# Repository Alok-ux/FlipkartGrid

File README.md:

# Flipkart Grid (Robotics)

TODO: Fill the readme
- [ ] Description of the project/event and upload the problem statement
- [ ] Team Description and also mention mentors
- [ ] Prerequisites and Installation procedure
- [ ] Run Instructions

Credits:
- [Multi-Agent Path Planning in Python
](https://github.com/atb033/multi_agent_path_planning.git)

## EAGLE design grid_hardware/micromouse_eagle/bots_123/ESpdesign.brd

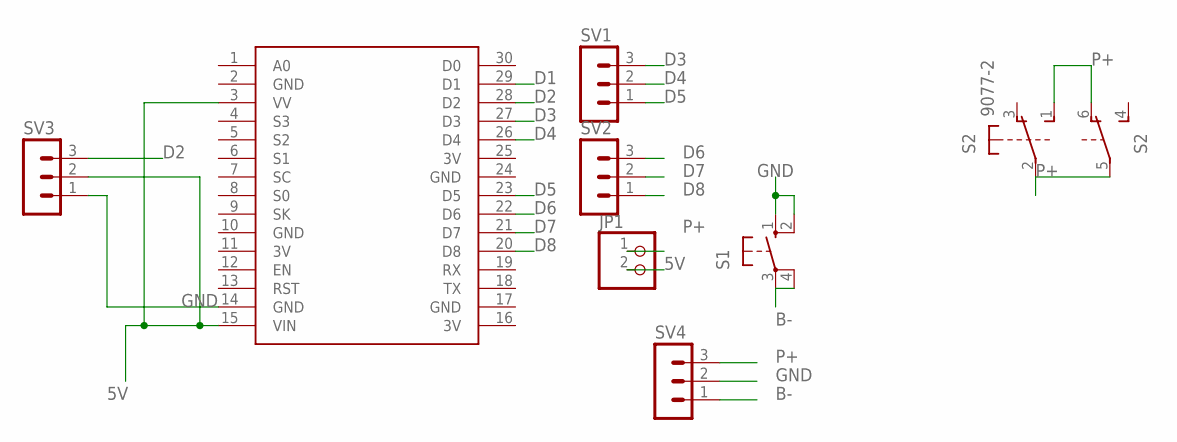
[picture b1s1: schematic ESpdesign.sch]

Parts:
JP1: PINHD-1X2; 1X02
S1: 10-XX; B3F-10XX
S2: 9077-2
SV1, SV2, SV3, SV4: MA03-1
U$1: NODEMCU

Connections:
3V: U$1.11 (3V), U$1.16 (3V), U$1.25 (3V)
5V: JP1.2, SV3.2, U$1.3 (VV), U$1.15 (VIN)
B-: S1.3, S1.4 (P1), SV4.1
D1: U$1.29 (D1)
D2: SV3.3, U$1.28 (D2)
D3: SV1.3, U$1.27 (D3)
D4: SV1.2, U$1.26 (D4)
D5: SV1.1, U$1.23 (D5)
D6: SV2.3, U$1.22 (D6)
D7: SV2.2, U$1.21 (D7)
D8: SV2.1, U$1.20 (D8)
GND: S1.1 (S), S1.2 (S1), SV3.1, SV4.2, U$1.2 (GND), U$1.10 (GND), U$1.14 (GND), U$1.17 (GND), U$1.24 (GND)
P+: JP1.1, S2.1 (S), S2.2, S2.5, S2.6 (O), SV4.3

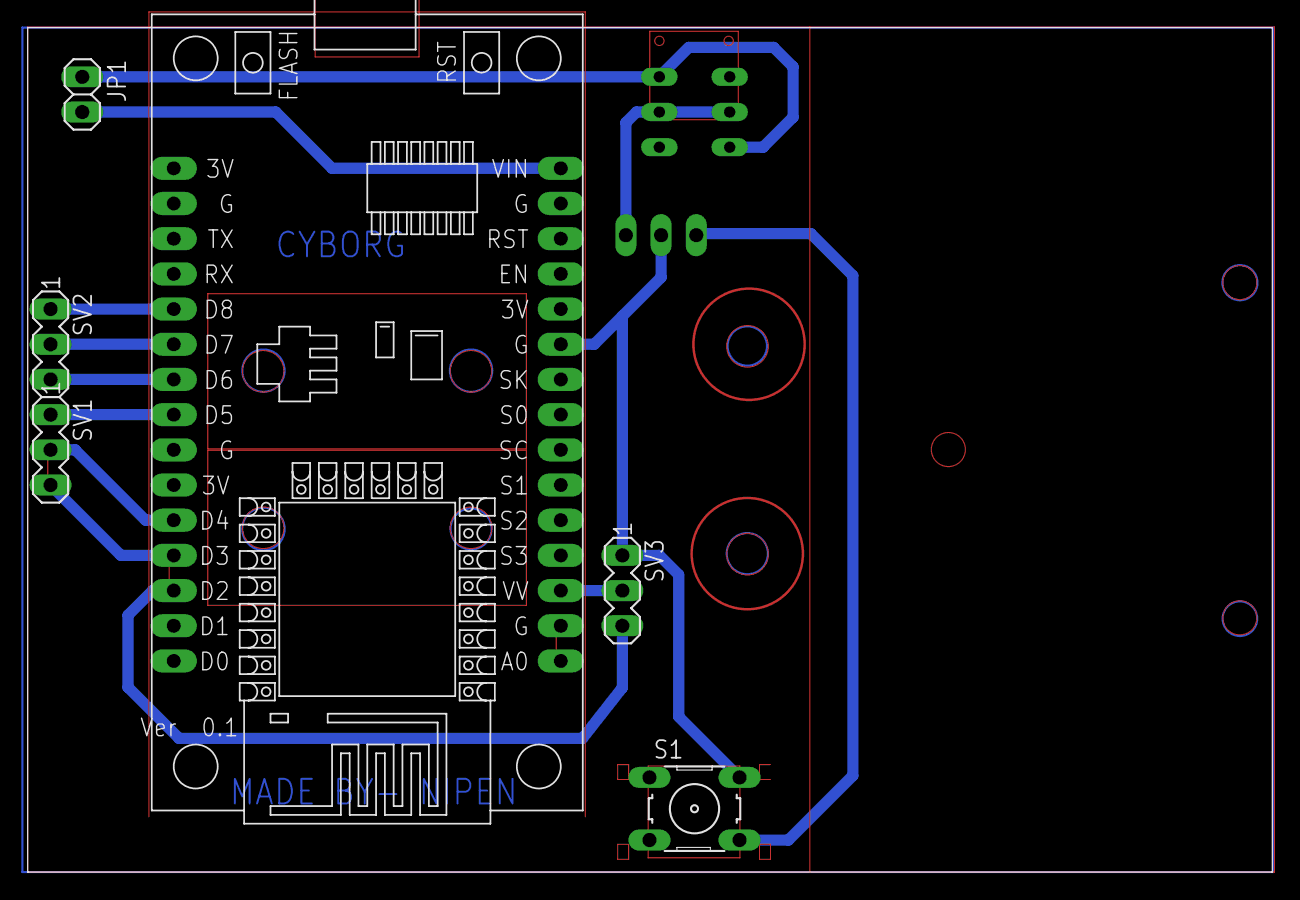
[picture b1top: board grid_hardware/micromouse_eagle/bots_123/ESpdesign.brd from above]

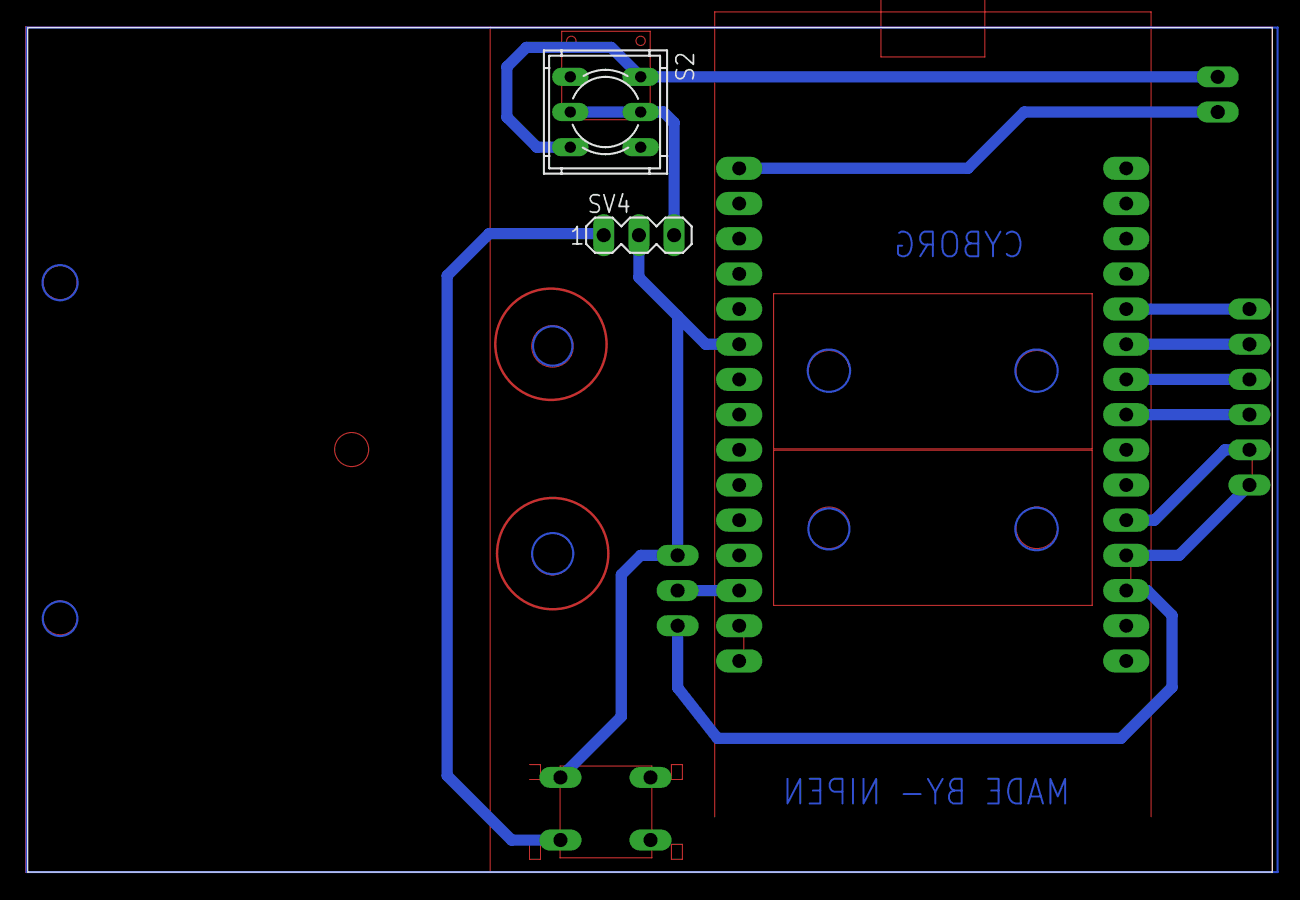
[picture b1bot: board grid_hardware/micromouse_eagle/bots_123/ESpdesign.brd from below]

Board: 2 copper layers, 89.8 x 61.0 mm, 8 parts (2 on the bottom side), 12 nets.

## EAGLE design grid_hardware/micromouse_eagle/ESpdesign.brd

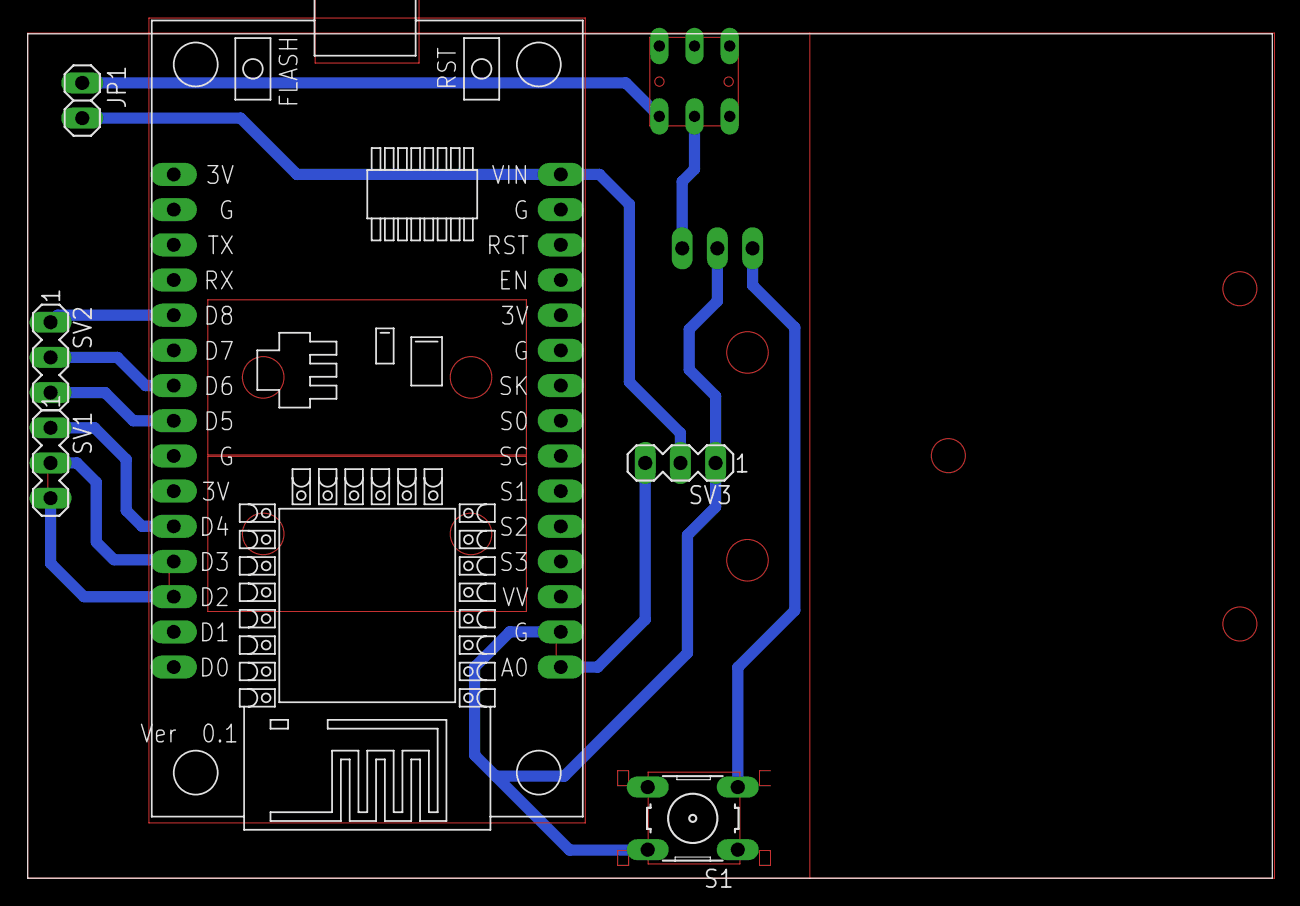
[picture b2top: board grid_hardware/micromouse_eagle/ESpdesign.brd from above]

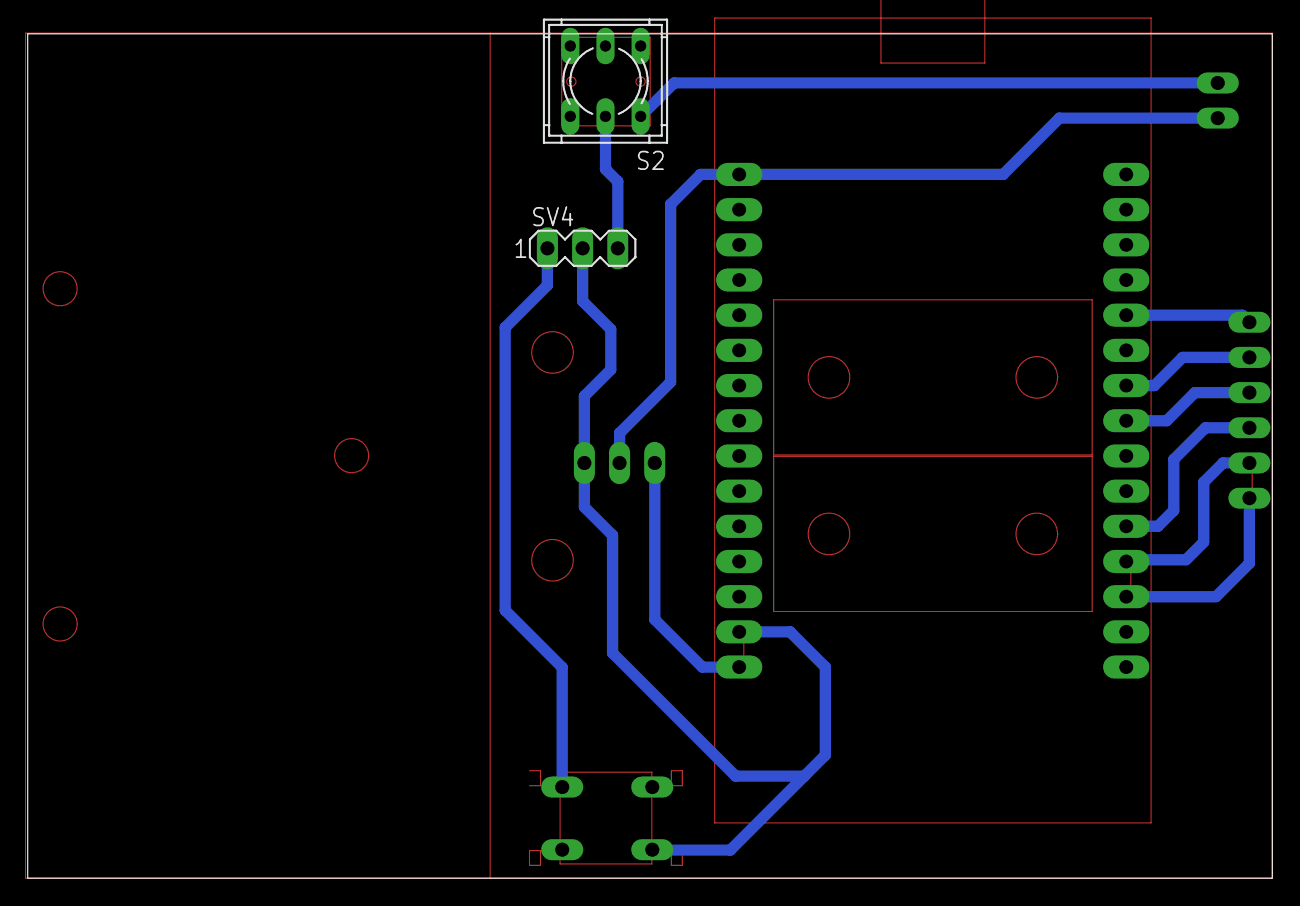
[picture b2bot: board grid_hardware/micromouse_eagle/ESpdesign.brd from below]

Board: 2 copper layers, 89.8 x 61.0 mm, 8 parts (2 on the bottom side), 12 nets.

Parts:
JP1: 1X02
S1: B3F-10XX
S2: 9077-2
SV1, SV2, SV3, SV4: MA03-1
U$1: NODEMCU

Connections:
3V: U$1.11, U$1.16, U$1.25
5V: JP1.2, SV3.2, U$1.15
A0: SV3.3, U$1.1
B-: S1.3, S1.4, SV4.1
D2: SV1.3, U$1.28
D3: SV1.2, U$1.27
D4: SV1.1, U$1.26
D5: SV2.3, U$1.23
D6: SV2.2, U$1.22
D8: SV2.1, U$1.20
GND: S1.1, S1.2, SV3.1, SV4.2, U$1.2, U$1.10, U$1.14, U$1.17, U$1.24
P+: JP1.1, S2.1, S2.2, SV4.3

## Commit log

2021-08-04 minor changes
2021-08-04 grid_arena & flipkart_grid pkg added
2021-08-05 added grid robot and apriltag detector packages
2021-08-08 april_tag & multi robot added
2021-08-08 change wheel dist
2021-08-09 changed few lines
2021-08-09 added a suscriber to camera image and changed cmakelist
2021-08-11 removed the while loop
2021-08-11 added apriltag detection algorithm
2021-08-19 added readme
2021-08-19 reverted changes
2021-08-20 added pid algorithm
2021-08-20 minor change
2021-08-20 added token
2021-08-20 made node2 executable
2021-08-21 added node for bot2
2021-08-21 integrated rqt_reconfigure
2021-08-21 fixed issues
2021-08-22 add nodes and communication between nodes
2021-08-23 trying to integrate dynamic reconfigure
2021-08-30 cam undistortion
2021-08-30 added the wifi code
2021-08-30 modified node2 to give direct binary values
2021-09-01 fisheye correction added
2021-09-01 regular push
2021-09-10 fisheye
2021-09-10 nodes for real testing
2021-09-10 fisheye_part
2021-09-14 Arduino Final Code
2021-09-15 cmake error due to python fixed
2021-09-15 grid pkg modified
2021-09-15 grid hardware modified
2021-09-16 mouse_click
2021-09-16 minor changes in grid_esp8266.ino
2021-09-17 added some modification
2021-09-17 added extreme ends
2021-09-17 changes in central
2021-09-17 grid_esp8266 modified
2021-09-17 routine push
2021-09-18 esp_websocket added
2021-09-18 modified push
2021-09-18 old push
2021-09-23 grid_esp8266.ino modified
2021-09-29 grid_array added & controller modified
2021-09-29 grid_array added
2021-10-02 added ignore
2021-10-02 major changes
2021-11-21 Solidworks Models
2021-11-22 solidworks modified and eagle project added
2021-12-03 micromouse_eagle added
2021-12-03 micromouse solidworks modified
2021-12-03 pcb dxf added
2021-12-03 new brd added
2021-12-03 brd continue
2021-12-04 sch, brd changed
2021-12-04 sch, brd of 123 and 4th bot changed
2021-12-13 added brd pdf
2021-12-27 controller added
2021-12-27 minor mod
2021-12-27 action server added
2021-12-27 data added
2021-12-27 empty pkgs added
2021-12-29 eagle files modified
2022-01-03 cbs added
2022-01-04 new cam driver added
2022-01-04 normal updates
2022-01-04 cam pose driver added
2022-01-04 routine update
2022-01-05 cbs changes
2022-01-05 controller & cam driver modified
2022-01-05 action_client modified
2022-01-05 action_server modified
2022-01-06 added values of i,j
2022-01-06 path planning for 4 bots initial
2022-01-07 basic updates
2022-01-07 action server modified
2022-01-07 controller minor change
2022-01-07 latest code
2022-01-07 static ip
2022-01-07 changes in action_client.py
2022-01-07 demo client modified
2022-01-07 client modified
2022-01-07 changes in path planning for 4 bots
2022-01-08 server modified
2022-01-08 change in cmake
2022-01-08 linear then angular & phi in goal added
2022-01-09 rot error fixed: rate.sleep()
2022-01-09 demo usable for 2 servers
2022-01-09 improvement in maneuvering
2022-01-09 action client modified & drop action added
2022-01-10 action client modified: send goal added
2022-01-16 visualizer added
2022-01-16 hyper_param modified
2022-01-16 city pose increase bug fixed
2022-01-16 grid data from phase1
2022-01-16 added mapping coordinates
2022-01-17 multi bot algo added in action_client.py
2022-01-17 init state bug fixed
2022-01-19 bot spec. modification
2022-01-19 standby bug fixed
2022-01-19 bot spec. modified
2022-01-19 bot spec changes
2022-01-19 bot id fixed
2022-01-19 dyn reconfig added
2022-01-20 test server added
2022-01-20 pkg id show added
2022-01-20 test server modified
2022-01-20 client standby bug fixed
2022-01-21 time overlay added
2022-01-22 cbs modified
2022-01-23 cbs modified and major changes
2022-01-23 drop location modified
2022-01-23 small grid approach
2022-01-23 cbs record
2022-02-06 last modified
